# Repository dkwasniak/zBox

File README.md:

# zBox

zBox is a custom offline NFC audio box I built for my daughter. It combines an ESP32, local SD card playback, a Raspberry Pi-hosted admin portal, LED effects, and a 3D-printed enclosure into a durable player that works with NFC cards.

This repository is the full build source for the project: firmware, backend, web admin, PCB design files, and the project documentation needed to rebuild it or adapt it for a similar box. The device plays audio stored on its SD card after an NFC tag is presented, and Wi-Fi is only used for sync and maintenance.

The box itself is built around a 3D-printed shell and custom electronics. This repository focuses on the complete hardware and software stack used in the build, from the ESP32 firmware and server to the PCB sources and operating notes. Mechanical exports such as the Fusion 360 STEP model live in `hardware/cad/fusion360/step/`.

## Project gallery

## Repository layout

```text
.
├── docs/                   Project documentation
├── esp32/                  ESP32 firmware (PlatformIO)
├── server/                 FastAPI backend and web admin UI
├── web/                    Static admin portal
├── hardware/               PCB, KiCad, Gerbers, and CAD exports
├── assets/                 Project photos and media used in docs
├── scripts/                Utility scripts
├── Dockerfile
└── docker-compose.yml
```

## Project split

- `esp32/` contains the offline playback firmware, Bluetooth audio pipeline, NFC handling, LED logic, and Sync Mode service flow.
- `server/` contains the FastAPI backend, SQLite integration, sync logic, and admin API.
- `web/` contains the static admin portal served by the backend.
- `hardware/pcb/kicad/` contains the PCB and schematic sources for the hardware build.
- `hardware/pcb/gerbers/` contains manufacturing outputs.
- `hardware/cad/fusion360/step/` contains exported mechanical CAD files such as STEP models.
- `assets/photos/` contains the product images used in this README.

## What to buy

If you want to build the current hardware revision, this is the practical shopping list. The various `PAD_*` items in KiCad are just solder pads for wires, not parts you need to buy.

- `1x` ESP32 Lolin D32 Pro
- `1x` PN532 NFC module that supports SPI mode
- `1x` MT3608 step-up module
- `1x` USB-C receptacle `GCT USB4085` or a compatible `USB 2.0 14-pin` footprint match
- `1x` P-channel MOSFET `AO3415A` in `SOT-23`
- `1x` NPN transistor `BC547` in `TO-92`
- `1x` electrolytic capacitor `470uF`
- `2x` resistors `5.1k`
- `1x` resistor `2.2k`
- `1x` resistor `10k`
- `1x` resistor `22k`
- `1x` resistor `100k`
- `1x` WS2812B LED strip or panel for the front light matrix
- `4x` momentary tactile buttons for `A`, `B`, `C`, and `D` — `12 × 12 × 7.3 mm`, 4-pin TACT switches with colored caps (e.g. MSALAMON kit or any equivalent 12 × 12 × 7.3 mm TACT switch)
- `1x` LiPo battery, currently `Akyga LP805080 3.7V / 4000mAh` with `JST 2-pin` connector
  This is the battery used in my build. Pack size: `8 mm` thick, `50 mm` wide, `80 mm` high. If you swap it for another pack, check the physical dimensions against the enclosure first.
- `1x` Bluetooth speaker, currently `JBL Go 2`
- hookup wire for all off-board connections

You will also need the non-electronic build parts:

- 3D-printed enclosure parts from the project CAD
- speaker holder inserts matching the audio setup you choose
- screws or other mounting hardware that fit your chosen assembly method

## Build cost

This is what I spent building one unit. Prices reflect individual-quantity purchases — buying components in bulk would bring the per-unit cost down.

| Part | Cost |
|------|------|
| PCB manufacturing | $5 |
| ESP32 Lolin D32 Pro | $15 |
| LiPo battery | $10 |
| Tactile buttons | $1 |
| Electronic components (resistors, caps, MOSFET, etc.) | ~$5–10 |
| 3D-printed enclosure filament | — |
| Bluetooth speaker (JBL Go 2) | had it at home |
| **Total (without speaker and filament)** | **~$36–41** |
| Enclosure design, prototype prints, and iteration | countless hours |
| Electrical prototyping and circuit debugging | countless hours |
| Fixing the low-quality software Claude Code produced | countless hours |

## Hardware overview

```text
NFC card
        │
        ▼
   PN532 reader
        │
        ▼
 ESP32 Lolin D32 Pro
   ├── SD card with local audio
   ├── WS2812B LED panel
   ├── buttons A / B / C / D
   ├── speaker power control
   └── Wi-Fi for sync and maintenance
        │
        ▼
 Bluetooth speaker
```

The device is offline-first during normal use. Audio and mappings live on the SD card, while Wi-Fi is only used for sync and maintenance.

## Audio design notes

For the current build I used a `JBL Go 2` connected over Bluetooth. It was a pragmatic choice: I already had that speaker at home, it was collecting dust, and I wanted the sound quality to stay reasonably good instead of dropping in a very cheap `2 USD` speaker.

I originally tried a direct wired path using a `PCM5102A` audio module and a jack connection into that speaker, but I could not get rid of the noise and crackling well enough to be happy with the result. Bluetooth ended up being the cleaner and more reliable solution for this revision.

The long-term plan is to reuse the speaker drivers from the JBL and connect them directly to the ESP32 through an `I2S Audio Amplifier Module NS4168`. The reason for that direction is simple: it should remove the extra Bluetooth speaker from the mechanical stack, give tighter integration with the enclosure, and keep a proper digital audio path from the ESP32 to the amplifier.

The speaker sits in a dedicated holder that slides onto internal rails built into the enclosure shell. The holder locks into position on those rails, so swapping it out for a different design requires no changes to the shell itself — print a new holder and slide it in. This makes it straightforward to adapt the enclosure for a different speaker body or a directly-wired driver setup without redesigning the main enclosure.

## PCB and schematic

> [!CAUTION]
> The PCB photo in this repository shows an earlier revision. The current schematic already includes corrections that came up after assembling the enclosure. If you are manufacturing a board, use the schematic and Gerbers from this repository — not the photo.

If you want to inspect or modify the hardware design, start here:

- Schematic: [zbox.kicad_sch](hardware/pcb/kicad/zbox.kicad_sch)
- PCB layout: [zbox.kicad_pcb](hardware/pcb/kicad/zbox.kicad_pcb)
- KiCad project: [zbox.kicad_pro](hardware/pcb/kicad/zbox.kicad_pro)
- Manufacturing outputs: [hardware/pcb/gerbers](hardware/pcb/gerbers)
- 3D enclosure export: [zbox_clear.step](hardware/cad/fusion360/step/zbox_clear.step)

## Printing the enclosure

The STEP model is ready to print. Each part must be printed separately. Print orientation matters:

| Part | Orientation |
|------|-------------|
| Shell (main body) | Standing upright on the front face |
| Side wall | Vertical |
| Front cover | No strong preference |
| Rear cover | Lying flat on its inner surface |

### Screws and heat-set inserts

| Location | Insert | Screw |
|----------|--------|-------|
| Rear cover | M3 heat-set inserts | M3 |
| Side wall mounting | — | M4 |
| ESP32 board mounting | — | M4 |

### Build notes

- The buttons are soldered onto a protoboard — there is no custom PCB for them. The build uses **12 × 12 × 7.3 mm momentary tactile switches (TACT, 4-pin)** with colored caps, from the MSALAMON kit. Any equivalent 12 × 12 × 7.3 mm TACT switch will fit.
- The cutout for the button board in the enclosure is not symmetric. This can be corrected in Fusion 360, or you can just account for it when positioning the buttons during soldering. It turned out that way, reason unknown.
- The button board is attached to the speaker enclosure with hot glue.

## Hardware disclaimer

I am self-taught when it comes to electronics, so the hardware part of this project may still contain mistakes, weak assumptions, or design issues that I am not aware of.

The current revision works for me in real use, but if you want to reuse, manufacture, or adapt it, treat the design as something to review carefully rather than as a guaranteed reference design. In classic programmer terms: it works on my desk.

## First build walkthrough

Complete flow from assembled hardware to first playback.

**1. Prepare the SD card**

Format the card as FAT32. A 4–16 GB card is sufficient for most use cases. Leave it empty — the sync operation creates the directory structure on the device automatically.

**2. Configure the firmware**

Open the server configuration and set `ZBOX_IP` in `.env` to the IP address or hostname of the ESP32. The admin portal uses this address to reach the device in Sync Mode.

**3. Flash the firmware**

```bash
cd esp32
pio run -t upload
```

**4. Start the server**

```bash
docker compose up -d --build
```

The admin portal is available at `http://<host>:8000`. Set `ZBOX_IP` in `.env` to the IP address or mDNS hostname of the ESP32 so the admin portal can reach the device for maintenance and sync.

**5. Pair the Bluetooth speaker**

See [Bluetooth pairing](#bluetooth-pairing) below.

**6. Add music and register NFC tags**

See [Adding music and NFC tags](#adding-music-and-nfc-tags) below.

**7. Sync**

Trigger a sync from the admin portal. The device must be on the same Wi-Fi network as the server. LEDs show yellow while Wi-Fi is active and a blue progress bar while files are transferring. After sync completes, presenting a registered NFC tag in Card Mode starts playback.

## Bluetooth pairing

The firmware connects to the Bluetooth speaker by name. The expected name is `JBL GO 2`, defined as `BT_SPEAKER_NAME` in `esp32/src/zbox_config.h`. If your speaker broadcasts a different name, update that constant before flashing.

To pair on first boot:

1. Power on the device (hold `D` for 0.8–2 sec from deep sleep).
2. Put the speaker into pairing mode.
3. The device scans for the speaker by name and connects automatically. LEDs show soft blue breathing while waiting.
4. Once connected, LEDs switch to green idle animation.

The connection is not persisted — the device reconnects by name on every boot.

## Adding music and NFC tags

The firmware plays **MP3 files only**. Other formats are not recognised.

**1. Upload a track**

Open the admin portal at `http://<host>:8000`, go to **Songs**, and upload an MP3 file.

**2. Register an NFC tag**

Go to **Tags**. Power on the ESP32 and hold an NFC tag over the PN532 reader — the portal shows the scanned UID once the device is connected. Assign a name to the tag and link it to a track.

**3. Sync**

After saving the mapping, trigger a sync from the portal. The server pushes the updated mappings and audio files to the device over Wi-Fi. Once sync finishes, presenting the tag in Card Mode starts the assigned track.

## Admin portal

The web admin portal runs at `http://<host>:8000` and covers everything needed to manage the device without touching the firmware.

### Dashboard

The dashboard shows the live device status at a glance: connection state, number of tracks and NFC tags in the library, battery level, system sounds assignment, and recently added tracks. If any tags have no track assigned, they are flagged here.

### Tracks

The Tracks section is the music library. You can add tracks by dragging and dropping an MP3 file, or by pasting a YouTube URL to import audio directly in the background. Each track shows its filename, upload date, and size. A built-in trim editor lets you clip the start and end of a track without re-uploading the file.

**YouTube import.** Paste any YouTube URL into the import panel, give the track a title, and the server downloads and converts the audio in the background. You can keep using the portal while it runs — the track appears in the library once the download is complete.

**Trim editor.** Each track has an in-browser trim editor. Set the start and end points to cut intros, silence, or anything you do not want to play on the device. The trimmed version is what gets synced to the SD card. Tracks with an active trim are marked in the library so you can tell them apart from the originals.

### NFC Tags

The NFC Tags section lists every registered tag with its name, UID, and assigned track. The quick assign panel on the right lets you pick a tag and a track and save the mapping in one click. You can also add a tag manually by typing its name and UID hex string — useful when you want to register a tag without having the physical device connected.

**Reading a tag UID with an Android phone**

The admin portal has a built-in NFC scanner that uses the Web NFC API — no separate app needed. It works only in **Chrome on Android**; on iPhone you need to enter the UID manually.

To use it directly from the portal:

1. Open the admin portal in Chrome on Android and go to the **Tags** section.
2. The scan card appears automatically if your browser supports Web NFC.
3. Tap **Scan** and hold the tag against the back of the phone.
4. The UID is read and pre-filled into the tag form.

Web NFC requires a secure context (HTTPS or localhost). If the portal is served over plain HTTP on your local network, Chrome will block it. To work around this, enable the following Chrome flag and add your server address to the allowlist:

```
chrome://flags/#unsafely-treat-insecure-origin-as-secure
```

Alternatively, install a standalone NFC reader app (e.g. **NFC Tools** by wakdev), read the UID from there, and paste it into the manual entry field in the portal.

### System Sounds

System Sounds are short audio clips the device plays for specific events: power off, switching to NFC mode, and switching to Music mode. Each slot shows a waveform preview and can be replaced with a custom MP3. The reset button restores the firmware defaults.

### Device and sync

The Device section is the maintenance hub. It shows live connection status, current mode, battery voltage, and SD card usage. The sync button pushes the current library and tag mappings to the device over Wi-Fi. Below that, a file browser shows everything on the SD card, and the diagnostic log viewer lets you stream or download device logs without a serial cable. The connection settings panel at the bottom is where you configure the device IP address for the portal.

## Getting started

### Server

```bash
docker compose up -d --build
```

The server runs in Docker. Runtime data is stored in `./data/`, audio assets in `./music/`, and the admin portal files in `./web/`, all mounted into the container by `docker-compose.yml`.

### ESP32 firmware

```bash
cd esp32
pio run
pio run -t upload
pio device monitor
```

The firmware depends on `esp32/lib/ESP32-A2DP`, which is kept as a Git submodule reference to the upstream project.

## Configuration model

- Server runtime configuration is local and installation-specific. The only required variable is `ZBOX_IP` — the IP address or mDNS hostname of the ESP32. Copy `.env.example` to `.env` and set it before starting the container.
- Wiring and GPIO pin assignments are documented in [`docs/hardware.md`](docs/hardware.md).

## Modes

- **Card Mode**. Default playback mode. The device reacts to NFC tags. Placing a known tag starts the assigned track from the SD card.
- **Music Mode**. Library playback mode. NFC is ignored and the buttons control pause, previous, and next track inside the local music library.
- **Light Mode**. Night light mode. Started from deep sleep by holding `D` longer during wake. In this mode `C` and `D` change brightness instead of volume.
- **Sync Mode**. Service mode used by the admin portal for maintenance, file transfer, log access, and configuration over Wi-Fi.

## Button shortcuts

| Button(s) | Action | Hold / Press | Context |
|-----------|--------|-------------|---------|
| `D` | **Power on** | hold `0.8–1.6 sec` while waking from deep sleep | from deep sleep |
| `D` | **Turn night light on** | hold `>= 1.6 sec` while waking from deep sleep | from deep sleep |
| `C` | **Power off** | hold `2 sec`, then release | Card Mode / Music Mode |
| `C` | **Emergency deep sleep** | hold `10 sec` | Card Mode / Music Mode |
| `C` | **Turn night light off** | hold `1 sec` | Light Mode |
| `B` | **Change mode: Music / Card** | hold `2 sec` | Card Mode / Music Mode |
| `A + B` | **Sync mode** | hold `2 sec` | Card Mode / Music Mode |
| `A` | **Battery level** | hold `2 sec` | Card Mode / Music Mode |
| `A` | **Pause / Resume** | short press | Music Mode |
| `A` | **Previous song** | double press | Music Mode |
| `B` | **Next song** | double press | Music Mode |
| `C` | **Vol −** | short press | Card Mode / Music Mode |
| `D` | **Vol +** | short press | Card Mode / Music Mode |
| `C` | **Light −** | short press | Light Mode |
| `D` | **Light +** | short press | Light Mode |

## LED animations

- **Boot progress**. Blue step-by-step progress. Each completed startup stage stays lit, and the current stage blinks three times.
- **Waiting for Bluetooth**. Soft blue breathing animation while the device is waiting for the speaker connection.
- **Idle**. Calm green breathing animation when the device is ready but not currently playing.
- **Playing**. Animated rainbow ring that reacts to audio energy and beats during playback.
- **Night Light**. Solid warm orange light. Brightness is controlled by `C` and `D`.
- **Volume**. Temporary white bar showing the current volume level for about one second after `Vol +` or `Vol -`.
- **Mode change**. Two short flashes. Music Mode uses the Music color, Card Mode uses the Card color.
- **Sleep ready**. Red blinking animation after holding `C` for two seconds. Releasing `C` at that point enters normal deep sleep.
- **Sync mode entry**. Purple animated dot pattern shown after `A+B` is held, while the device is preparing to reboot into Sync Mode.
- **Wi-Fi sync**. Blue blinking after the reboot, while the device is connecting to Wi-Fi and exposing the service endpoints used by the admin portal.
- **Sync progress**. Blue progress bar that fills while files are transferred to the SD card during sync.
- **Warning**. Slow amber breathing pulse when a mapping or file is missing.
- **Shutdown**. Purple sweep animation before the device powers down.
- **Battery check**. A color-coded bar on the LEDs: blue for high charge, then green, yellow, orange, and red for critical battery.

## Emergency deep sleep

**Emergency deep sleep** is a forced low-power shutdown triggered by holding `C` for `10 sec`.

- It is intended as a fallback if the normal shutdown path is not enough.
- It skips the regular graceful flow and shuts the device down as directly as possible.
- It still tries to turn the speaker off first if the hardware status line says the speaker is on.

## Deployment shape

The intended deployment is:

1. Build and run the FastAPI server in Docker on a small Linux host such as a Raspberry Pi.
2. Flash the ESP32 and configure the server to reach it via `ZBOX_IP`.
3. Use the web admin portal to manage tracks, NFC mappings, system sounds, and sync operations.

## Documentation

- [Server docs](docs/server.md)
- [Hardware docs](docs/hardware.md)
- [ESP32 quick start](esp32/README.md)

## Known constraints

- Playback is offline-first. The device syncs files and metadata to the SD card instead of streaming during normal use.
- Bluetooth and Wi-Fi are intentionally not used at the same time on the ESP32 due to memory and radio constraints.
- The current firmware configuration still requires a compile-time server host value.

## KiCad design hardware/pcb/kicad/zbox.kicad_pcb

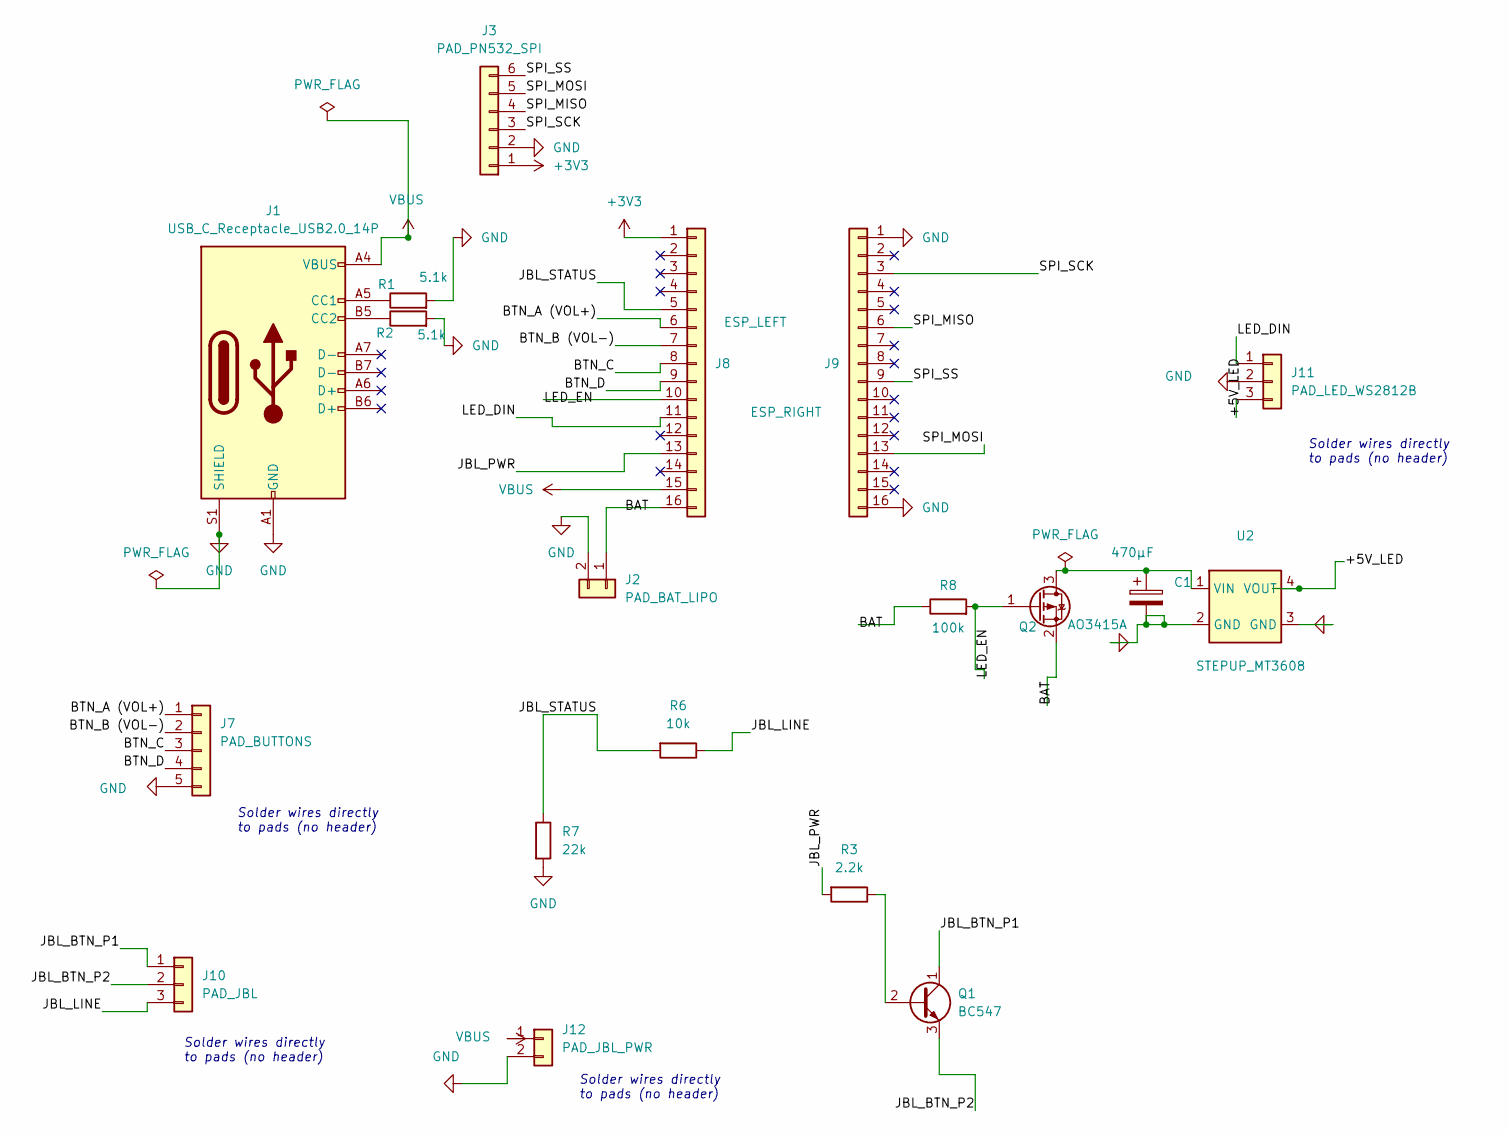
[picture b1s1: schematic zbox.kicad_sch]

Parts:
C1: 470µF; CP_Radial_D8.0mm_P3.50mm
J1: USB_C_Receptacle_USB2.0_14P; USB_C_Receptacle_GCT_USB4085
J2: PAD_BAT_LIPO; SolderPad_1x02_W2.2mm_H3mm_P2.7mm
J3: PAD_PN532_SPI; SolderPad_1x06_W2.2mm_H3mm_P2.7mm
J7: PAD_BUTTONS; SolderPad_1x05_W2.2mm_H3mm_P2.7mm
J8: ESP_LEFT; PinHeader_1x16_P2.54mm_Vertical
J9: ESP_RIGHT; PinHeader_1x16_P2.54mm_Vertical
J10: PAD_JBL; SolderPad_1x03_W2.2mm_H3mm_P2.7mm
J11: PAD_LED_WS2812B; SolderPad_1x03_W2.2mm_H3mm_P2.7mm
J12: PAD_JBL_PWR; SolderPad_1x02_W2.2mm_H3mm_P2.7mm
Q1: BC547; TO-92_Inline
Q2: AO3415A; SOT-23
R1, R2: 5.1k; R_Axial_DIN0207_L6.3mm_D2.5mm_P10.16mm_Horizontal
R3: 2.2k; R_Axial_DIN0207_L6.3mm_D2.5mm_P10.16mm_Horizontal
R6: 10k; R_Axial_DIN0207_L6.3mm_D2.5mm_P10.16mm_Horizontal
R7: 22k; R_Axial_DIN0207_L6.3mm_D2.5mm_P10.16mm_Horizontal
R8: 100k; R_Axial_DIN0207_L6.3mm_D2.5mm_P10.16mm_Horizontal
U2: STEPUP_MT3608; MT3608_Pancake

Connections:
+3V3: J3.1, J8.1
/+5V_LED: J11.3, U2.4 (VOUT)
/BAT: J2.1, J8.16, Q2.2 (S), R8.1
/BTN_A (VOL+): J7.1, J8.6
/BTN_B (VOL-): J7.2, J8.7
/BTN_C: J7.3, J8.8
/BTN_D: J7.4, J8.9
/JBL_BTN_P1: J10.1, Q1.1 (C)
/JBL_BTN_P2: J10.2, Q1.3 (E)
/JBL_LINE: J10.3, R6.1
/JBL_PWR: J8.13, R3.2
/JBL_STATUS: J8.5, R6.2, R7.1
/LED_DIN: J8.11, J11.1
/LED_EN: J8.10, Q2.1 (G), R8.2
/SPI_MISO: J3.4, J9.6
/SPI_MOSI: J3.5, J9.13
/SPI_SCK: J3.3, J9.3
/SPI_SS: J3.6, J9.9
GND: C1.2, J1.A1 (GND), J1.A12 (GND), J1.B1 (GND), J1.B12 (GND), J1.S1 (SHIELD), J2.2, J3.2, J7.5, J9.1, J9.16, J11.2, J12.2, R1.2, R2.2, R7.2, U2.2 (GND), U2.3 (GND)
unnamed: J1.A5 (CC1), R1.1
unnamed: J1.B5 (CC2), R2.1
unnamed: Q1.2 (B), R3.1
unnamed: C1.1, Q2.3 (D), U2.1 (VIN)
VBUS: J1.A4 (VBUS), J1.A9 (VBUS), J1.B4 (VBUS), J1.B9 (VBUS), J8.15, J12.1

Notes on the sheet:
Solder wires directly to pads (no header)

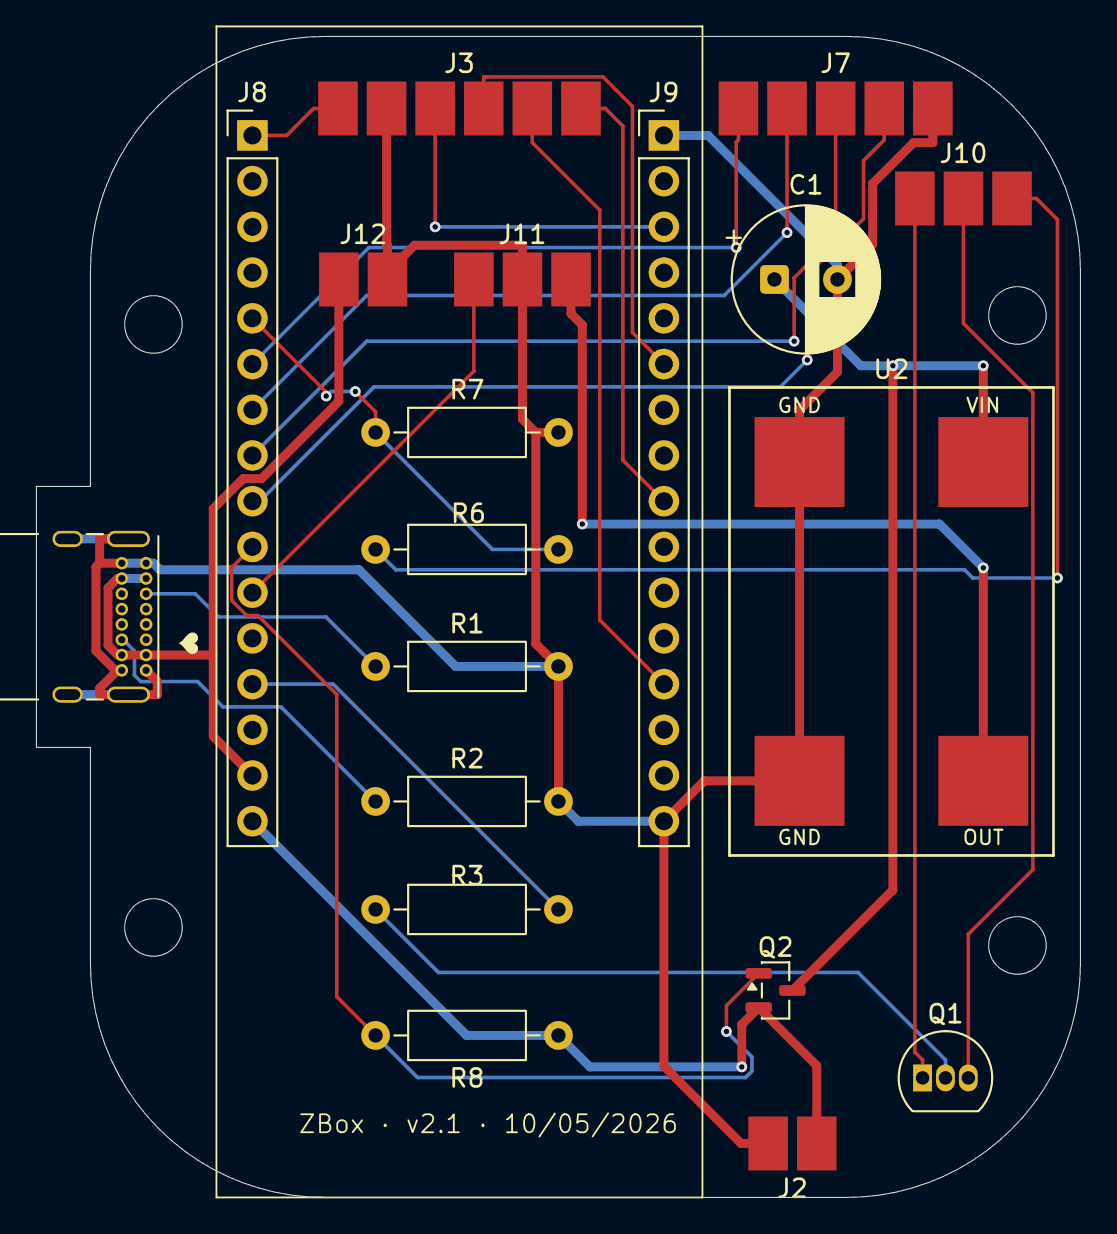
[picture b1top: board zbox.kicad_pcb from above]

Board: 2 copper layers, 58.0 x 64.5 mm, 19 parts (0 on the bottom side), 24 nets.

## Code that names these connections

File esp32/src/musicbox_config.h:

#pragma once

#define ENABLE_LEDS true

// =============================================================================
// PINY
// =============================================================================

#define SD_CS 4 // SD Card CS (wbudowany slot Lolin D32 Pro)

// PN532 NFC (Software SPI)
#define PN532_SCK 22
#define PN532_MISO 21
#define PN532_MOSI 0
#define PN532_SS 5

#define LED_PIN 14  // WS2812B DIN
#define LED_EN  27  // P-MOSFET gate (AO3415A): LOW = LEDy ON, HIGH = OFF
#define LED_COUNT 12
#define LED_BRIGHTNESS 40

#define BTN_A 32 // wolny  (RTC)
#define BTN_B 33 // wolny  (RTC)
#define BTN_C 25 // VOL-   (RTC)
#define BTN_D 26 // VOL+   (RTC, wake-up z deep sleep przez ext0)
#define BTN_COUNT 4

#define JBL_POWER 13  // Tranzystor NPN -> przycisk POWER na JBL
#define JBL_STATUS 34 // ADC - linia statusowa JBL (dzielnik 10k/22k)
#define BAT_ADC_PIN 35 // GPIO35 (I35) - onboard D32 Pro dzielnik 100k/100k VBAT->I35->GND
#define BAT_ADC_DIVIDER_RATIO 2.0f // schemat D32 Pro: VBAT --100k-- GPIO35 --100k-- GND
#define BAT_ADC_CALIBRATION 0.983f // kalibracja pod realny egzemplarz po ustabilizowaniu toru ADC

// =============================================================================
// KONFIGURACJA
// =============================================================================

#define BT_SPEAKER_NAME "JBL GO 2"

#define LONG_PRESS_MS 2000
#define DOUBLE_CLICK_WINDOW_MS 350
#define EMERGENCY_SLEEP_MS 10000
#define WAKE_ABORT_MS 800
#define WAKE_NIGHT_LIGHT_MS 1600
#define NIGHT_LIGHT_SLEEP_HOLD_MS 1000
#define DEBOUNCE_MS 50
#define NFC_READ_INTERVAL 1000
#define NFC_ERROR_THRESHOLD 10
#define NO_TAG_THRESHOLD 2
#define NFC_TAG_LOST_MS 3000  // wymagany ciągły brak odczytu, zanim uznamy kartę za zdjętą
#define PN532_WAKEUP_SPI 0x20
#define PN532_WAKE_SETTLE_MS 5
#define AUDIO_BUF_SIZE 2048

// JBL
#define JBL_POWER_PRESS_MS 500
#define JBL_STATUS_THRESHOLD 500  // ~0.4V — powyżej residual/noise, poniżej ON (~2V+)
#define JBL_BOOT_WAIT_MS 5000 // timeout na cold boot JBL + A2DP reconnect

// Głośność Bluetooth (AVRCP)
#define BT_VOL_STEP 5
#define BT_VOL_MIN 0
#define BT_VOL_MAX 100
#define BT_VOL_DEFAULT 50
#define NIGHT_LIGHT_BRIGHTNESS_STEP 10
#define NIGHT_LIGHT_BRIGHTNESS_MIN 10
#define NIGHT_LIGHT_BRIGHTNESS_MAX 100
#define NIGHT_LIGHT_BRIGHTNESS_DEFAULT 50

// Idle timeout → deep sleep
#define IDLE_TIMEOUT_MS (10UL * 60 * 1000) // 15 minut bez odtwarzania
#define NIGHT_LIGHT_TIMEOUT_MS (15UL * 60 * 1000)

// Sync
#define SERVER_HOST "<musicbox-server-ip>"
#define SERVER_PORT 8000
#define HTTP_TIMEOUT 15000
#define DOWNLOAD_BUF_SIZE 16384

// Diagnostic mode
#define DIAG_PENDING_PATH "/data/diag_pending"
#define DIAG_AP_NAME "zBox-Diag"
#define DIAG_HTTP_PORT 80
#define DIAG_OTA_PORT 3232
#define DIAG_LOG_INTERVAL_MS 5000

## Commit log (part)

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2026-01-29 working with javk
2026-02-26 lolin impl for yoto
2026-03-20 dziala ale szumi
2026-03-24 workin bt solution
2026-03-24 claude files
2026-04-10 wyczyszczony kod, 4 przyciski, stary schemat kikad
2026-04-29 mvp 1.1
2026-04-30 ogolnie dziala. Sa juz dzwieki przy deep sleep i sync
2026-04-30 dziala wlaczanie kiedy trzeba
2026-04-30 status baterii
2026-05-01 przed refaktorem przyciskow na osobny task
2026-05-01 przed refaktorem
2026-05-01 zmiana mosi z gipo 12 na gipo 0 - dziala
2026-05-02 dziala wybudanie i usypianie nfc
2026-05-02 po refactorze, przed review
2026-05-02 dziala odczyt baterii
2026-05-02 dziala wszystko, mozna sie bawic aniamcjami
2026-05-03 karta w slocie nie odtwarza ponownie, beat animacja
2026-05-03 music mode, card mode
2026-05-03 updated gitignore
2026-05-05 dziala wszystko, zmiana sync mode gotowa
2026-05-07 dziala przed trybem lampki
2026-05-08 dziala
2026-05-08 for github
2026-05-10 after refactor
2026-05-10 updated photos
2026-05-10 updated docs
2026-05-10 doku
2026-05-13 cleanup
2026-05-13 reverted diagnostic mode
2026-05-16 glosnik przez modul dziala i naprawione bugi po refacotrze oraz kilka usrpawnien
2026-05-17 poprawki dla trybu BT
2026-05-31 dziala bez BT
2026-06-01 dziala, 1.0
2026-06-01 wszystko dziala, nie dziala rozlaczanie slcuhawek bo crash
2026-06-01 wszystko smiga, nie dotykac bo wybuchnie
